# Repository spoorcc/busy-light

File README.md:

<div align="center">

# busy-light

**A Wi-Fi status ring for desks, doors and build rooms.**
Sixteen RGB LEDs that show your Jenkins build status or any other level, with no app and no cloud account.

-003399)

[Documentation](docs/README.md) ·
[Requirements](docs/requirements/needs.md) ·
[Architecture decisions](docs/decisions/) ·
[Roadmap](#roadmap) ·
[Contributing](CONTRIBUTING.md) ·
[Security](SECURITY.md)

</div>

---

> **Honest status:** busy-light is in the **design phase**. There is no released firmware, no manufactured
> hardware and no approved requirement set yet. Everything below describes the **intended** product and
> what the project has already proved with desk studies, PC prototypes and CAD experiments.
> Nothing here is certified, and no conformity with any regulation is claimed.

## What is it?

busy-light is a small round device with a ring of 16 individually controllable RGB LEDs. It joins your Wi-Fi,
listens to your build server or fetches its status over REST, and turns that into a colour or a level you can see
from across the room.

The first use case is a **Jenkins build light**: green, red, unstable, running, aborted. The second is a
**level gauge**: the ring fills like a dial from 0 to 100 percent for queue length, test pass rate, or any number
a REST endpoint can give.

## Why another status light?

Most status lights need a vendor app, a cloud account or a USB cable to a PC. busy-light is designed around a
different set of goals.

| Goal | What it means |
|------|---------------|
| **Works on a shared, untrusted network** | Per-unit access point password, encrypted provisioning, authenticated and signed updates. |
| **No app, no cloud** | Set-up and configuration through a web page served by the device itself. |
| **Small enough to put anywhere** | About 53 mm across, powered over USB-C. |
| **Cheap to build** | Target assembled board cost of EUR 10 to 20 with a prototype shop. |
| **Source-available and reproducible** | Software, hardware and mechanics are all in this repository, with generated files and checks that anyone can rerun. Code is Apache-2.0. Documentation, hardware and mechanics are free to copy and build for non-commercial use. |
| **Built like a product** | Requirements, decisions, risks and tests are traced from the first line, with EU market access (CE) in mind from day one. |

## Planned features

These are **planned**, taken from the draft requirements in [`docs/requirements/`](docs/requirements/). None is released.

- **16-LED RGB ring** with status colours, animations and a level (gauge) mode
- **Jenkins first:** receive pushed build events, or poll the Jenkins REST API
- **Mapping without code:** pick a value in the JSON answer, map it to a state or scale it to a level
- **Own access point for set-up:** the device creates a Wi-Fi network with a unique password printed on a label, you open a web page and enter your Wi-Fi details
- **Web interface** served by the device, no app to install
- **WPA2 and WPA2-Enterprise** networks, with user-loadable certificates
- **Over-the-air updates** that are signed and can be checked before they run
- **USB-C power** with safe handling of the available current: a hardware current limit and a firmware limiter on LED brightness
- **Secure boot and flash encryption** (planned for production units)

```mermaid
flowchart LR
    J[Jenkins or other REST source] -- push or poll --> D((busy-light))
    P[Phone or laptop] -- set-up page over the device's own Wi-Fi --> D
    D --> R[16-LED ring]
    U[USB-C] -- power --> D
```

## What exists today

The project has done a lot of thinking and some experiments, but **no product code or hardware yet**.

| Area | State |
|------|-------|
| Requirements | Written for needs, system, software, hardware and mechanics (101 entries). **18 are approved by the owner** (all 9 mechanical, 5 software, 3 hardware including the current-limit gate HW-010, 1 system); the rest are drafts. |
| Architecture decisions | 19 decision records. **17 are accepted** by the owner (ADR-0011, the housing, only for the prototype); 2 are superseded. Recent decisions: first antenna layout (ADR-0003), annular back bayonet (ADR-0014), AND gate for the fault readback (ADR-0018) and a standard-package regulator with a firmware current limit (ADR-0019). |
| Risk register | Open. Each risk has a mitigation and a verification link. |
| Reviews | Independent "goldfish" reviews recorded for the system design, the first spike plan and the hardware flow decision ([`docs/reviews/`](docs/reviews/)). |
| Software | Zephyr 4.5.0 workspace pinned. The input-current gate logic (`sw/app/src/gate.c`) has **20 host unit tests that pass** on `native_sim`; nothing runs on a board. A mapping extractor and an LED current limiter were tried as PC-only prototypes (results in the reports, code not in `sw/`). |
| Hardware | A scripted KiCad flow produces a **spike** full-board schematic (USB-C input, current-limit gate, hold-off, AND-gate fault readback, supply-pin surge protection, ESP32-C3 module, 16 LEDs) and a 4-layer board on the mechanical-spike outline, routed with Freerouting. The board is routed with **0 unconnected items** and passes the strict check apart from tolerated antenna and stand-in findings, but nothing is reviewed. Part datasheet evidence is recorded in a schema, **none verified**. The surge on the 5 V side is still to be **measured** on a built board. **No product schematic or layout yet.** |
| Mechanics | FreeCAD scripts generate the housing (base with USB-C window, button hole, PCB posts and snap hooks, annular back bayonet with lock lips and a mating accessory ring, lid with snap bumps), print coupons for the diffuser and the bayonet, and a tolerance check with tests. **Nothing printed or fit-tested**; the tolerances are assumptions. |
| Regulatory | Applicability analysis and compliance matrix started. No evidence collected, no declaration made. |

The reports behind these lines are in [`docs/verification/reports/`](docs/verification/reports/).

### Gallery

All images are generated from text sources or tool exports; none is hand-drawn. None shows a product design: they show the proposal and the experiments.

**Proposed software blocks** (PlantUML source in [`docs/diagrams/plantuml/`](docs/diagrams/plantuml/), draft architecture):

**Hardware spike (KiCad 10, generated by script, not reviewed, not the product design):**

| Schematic (spike), part 1: USB-C input, CC detection, current-step gate, hold-off, regulator |
|---|
|  |

| Schematic (spike), part 2: ESP32-C3 module, button, AND-gate fault readback, LED buffer, 16 LEDs |
|---|
|  |
| Two crops of one single-sheet schematic, exported with `kicad-cli`; click an image for full size. Some labels overlap (for example C1 and C27) and part values are open (`tbd`). The schematic is a spike under ADR-0012 (Proposed), not reviewed and not approved. |

| Board, 4 layers, top view (3D render) | Board, all copper layers and silkscreen |
|---|---|
|  |  |
| Generated by script from the schematic netlist on the outline of the mechanical spike. The 16 LED cells (one 2020 LED with its capacitor) are placed and routed as a symmetric ring by script; the rest is routed with Freerouting v2.5.0 (fine rules, 0.1 mm tracks, see ADR-0020, Proposed). | One run (ring14 run 9), picked as the best of 12 (routing is not deterministic); the board is stored in [`hw/kicad/spike-gate/board/`](hw/kicad/spike-gate/board/). **0 unconnected items, 0 hard findings.** The strict check lists 11 findings, all in the classes that the waiver list tolerates: 8 courtyard overlaps and 1 item inside the rule area (ESP32 antenna keep-out), 2 symbol mismatches (C3, C4). Power paths (analyst assumptions of 1.5, 1.0 and 0.5 A): 13.5, 18.0 and 22.7 mV drop. The fabricator-minimum check passes for the JLCPCB numbers of ADR-0020 (Proposed), with the via ring at the 0.15 mm minimum. Not run: antenna/RF, thermal, full fab review, bench. A spike result, **not** a reviewed board. |

Regenerate with [`hw/kicad/spike-gate/render_readme_images.sh`](hw/kicad/spike-gate/render_readme_images.sh). The 3D render has no component models for most parts and is not a fit check. See [`spike-pcb-placement-routing.md`](docs/verification/reports/spike-pcb-placement-routing.md).

| Housing model (FreeCAD script), exploded | Back of the base |
|---|---|
|  |  |
| Generated by [`mech/freecad/housing.py`](mech/freecad/housing.py) and [`accessory.py`](mech/freecad/accessory.py), drawn by [`mech/render_readme_images.sh`](mech/render_readme_images.sh). Parts: lid with snap bumps, base with USB-C window, button hole (working values, the switch is not chosen), posts, snap hooks and the bayonet groove with lock lips, stop and detent; the orange ring is the accessory with three T-lugs. The model passes its own checks (valid solids, no overlap, board fits, the lock holds and stops). **Nothing is printed or fit-tested**; the release tab is not modelled. Results: [`mech-housing-first-model.md`](docs/verification/reports/mech-housing-first-model.md). |

## Roadmap

| Phase | Goal | State |
|-------|------|-------|
| **0. Foundation** | Process, requirements, decisions, risks, regulatory outline, CI | in progress |
| **1. Spikes** | Prove the risky parts on a dev kit: Wi-Fi access point, web page, LED drive, power budget, secure boot | planned, waiting for approval of the spike plan |
| **2. Prototype** | 10 internal prototypes: schematic, board, housing, first firmware | planned |
| **3. Verify** | Test cases against approved requirements, pre-compliance tests | planned |
| **4. Release candidate** | Signed firmware, documentation, technical file | planned |

Dates are deliberately not given. Phases start when the previous one has evidence.

## How the project works

busy-light is run like a small regulated company, because the goal is a product that could be sold.

- **Specification before implementation.** No firmware, board or housing change without an approved requirement it traces to.
- **Decisions are recorded.** Costly choices get an architecture decision record with real alternatives, weighted criteria and a critical review.
- **Evidence over claims.** A result is only reported with its test or analysis. What was not run is stated.
- **Everything is code.** Diagrams, hardware (KiCad files generated from scripts) and mechanics (FreeCAD from scripts) are text sources with checks in CI.
- **Documentation is part of the product.** User documentation follows a controlled-language standard (ASD-STE100 principles).
- **EU market access from the start.** Cyber Resilience Act, Radio Equipment Directive, RoHS and friends are tracked in [`docs/regulatory/`](docs/regulatory/README.md). The project states which evidence exists and never states that the product "is compliant".

The full process is in [`docs/process/README.md`](docs/process/README.md).

## Repository layout

| Path | Contents |
|------|----------|
| [`sw/`](sw/) | Zephyr application, west manifest, tests |
| [`hw/`](hw/) | KiCad project, simulation, fabrication outputs, datasheets |
| [`mech/`](mech/) | FreeCAD models, exports, drawings, analysis |
| [`docs/`](docs/README.md) | Process, requirements, architecture, decisions, risk, verification, regulatory, user docs, standards |
| [`scripts/`](scripts/) | Traceability, documentation and CI check scripts |

## Getting started (developers)

**Software** (needs the Zephyr SDK and `west`):

```sh
west init -l sw
west update
west build -b <board> sw/app
```

**Repository checks:**

```sh
python3 -m venv --system-site-packages .venv
.venv/bin/pip install --group dev --group hw
python3 -I scripts/check_traceability.py     # requirements, decisions, risks and tests are linked
python3 -I scripts/check_docs_style.py       # user documentation style
scripts/build_diagrams.sh --check            # diagrams are up to date
.venv/bin/ruff check . && .venv/bin/pytest   # Python tooling
```

**Hardware and mechanical checks** run in CI through `scripts/ci_hw.sh` (KiCad 10) and `scripts/ci_mech.sh` (FreeCAD).
They report **NOT RUN** until product sources exist, so a skipped check is never mistaken for a pass.

## Contributing

Ideas, reviews and critical questions are welcome. Pull requests with code or documents are not accepted until the contributor terms have had a legal check. Please read [`CONTRIBUTING.md`](CONTRIBUTING.md) first.
A good first contribution is to challenge a draft requirement or a proposed decision in
[`docs/decisions/`](docs/decisions/): write down the alternative you would pick and why.

## Security

busy-light is designed for shared networks. To report a vulnerability, follow [`SECURITY.md`](SECURITY.md).
The planned vulnerability handling and key management are drafts under
[`docs/regulatory/technical-file/05-cybersecurity/`](docs/regulatory/technical-file/05-cybersecurity).

## License

| Part | Licence |
|------|---------|
| Code (firmware, scripts, generators, CI, assistant instructions in `.claude/`) | [Apache-2.0](LICENSES/Apache-2.0.txt) |
| Documentation, hardware, mechanics, images | [CC BY-NC-SA 4.0](LICENSES/CC-BY-NC-SA-4.0.txt) |
| Commercial use of the hardware, mechanics or documentation | Separate licence from the owner |

You may copy, study and build from the hardware and mechanical files for non-commercial purposes. Using a unit that you
bought is not restricted. The non-commercial parts are **source-available, not open source hardware**.
Details and the path-by-path map are in [`LICENSE.md`](LICENSE.md) and [`REUSE.toml`](REUSE.toml);
the decision is [ADR-0015](docs/decisions/ADR-0015-licensing-corrections.md). Third-party parts such as Zephyr keep their own licences.
This is not legal advice.

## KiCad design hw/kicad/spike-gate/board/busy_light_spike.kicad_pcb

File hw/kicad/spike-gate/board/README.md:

# Spike board result (HW-010)

The routed 4-layer spike board: ring14 run 9, picked from 12 runs (Freerouting 2.5.0 is not deterministic, so this is one run, not a recipe).
Made by `run_best.sh` with `SPIKE_PROFILE=fine`, `PLACE_GRID=1.0`, `PLACE_ANT_KEEPOUT=1`, `PLACE_BLOCKS=3`, `PLACE_ORIENT=1.5`, `SEED_OFFSET=200`, input netlist `full8` (not in the repo; regenerate with `run_full.sh`). Report: `docs/verification/reports/spike-pcb-placement-routing.md`.

Files: `busy_light_spike.kicad_pcb`, `.kicad_pro`, `.kicad_sch`, `.kicad_dru` (rules), `.placement.json`, `fp-lib-table` and `CUSTOM.pretty` (open the board next to them). Script output, never edited by hand.

Finishing (2026-11-08): the seven unannotated parts were renamed (`src/pcb_rename.py`: C1B to C1F are now C27 to C31, R_ILIM3B is R20, R_VD is R21), and silkscreen designators and four fiducials were added (`src/pcb_finish.py`; 27 parts have no free place for a designator). Routing did not change.

Checks run on this file (2026-11-08):
- strict gate `SPIKE_ALLOW_KNOWN_OPEN=0 python3 src/kicad_strict.py drc board/busy_light_spike.kicad_pcb stitched-4l`: 0 open items, only the tolerated classes: courtyards_overlap 8 (max 14, U9 antenna, DEV-004), items_not_allowed 1 (DEV-004);
- `src/pcb_fabcheck.py`: PASS against the JLCPCB numbers of ADR-0020, with the via ring at the absolute minimum (0.15 mm) on all 131 vias;
- `src/pcb_power_check.py`: 13.5 mV (VBUS_IC, 1.5 A), 18.0 mV (+5V, 1.0 A), 22.7 mV (+3V3, 0.5 A); the 50 mV target is an analyst assumption, not a requirement.

Capacitor values and spare (2026-11-08, owner decisions in `docs/verification/reports/proposal-tbd-capacitor-values.md`): C2 4.7u, C3 10u (0805), C5 2.2u, C6 10u; C4 and C32 are 1206 spares, not fitted (HW-016). `src/pcb_spare_caps.py` set the values, added C32 (bottom side, 24 mm from U7 pin 6 because the top side has no free place; C4 is 8.2 mm away, so the [5] mm of HW-016 is not met by either), marked both do-not-populate and wrote the sourcing fields to the footprints; `pcb_fix.py` routed C32 (one via, 13.7 mm of track, nothing else moved). The strict gate has no footprint mismatch any more; power drops unchanged (13.5, 18.0, 22.7 mV).

Not run: antenna/RF, thermal, a full fab review (Gerber, silkscreen, solder mask, assembly), bench. Open: ADR-0020 (fine rules) is Proposed; HW-014 to HW-016 are Draft. The test points are not in a row and the IC rotations are mixed. This is a spike result, not a reviewed or approved board; it is not "DFx approved" and not "fully functional".

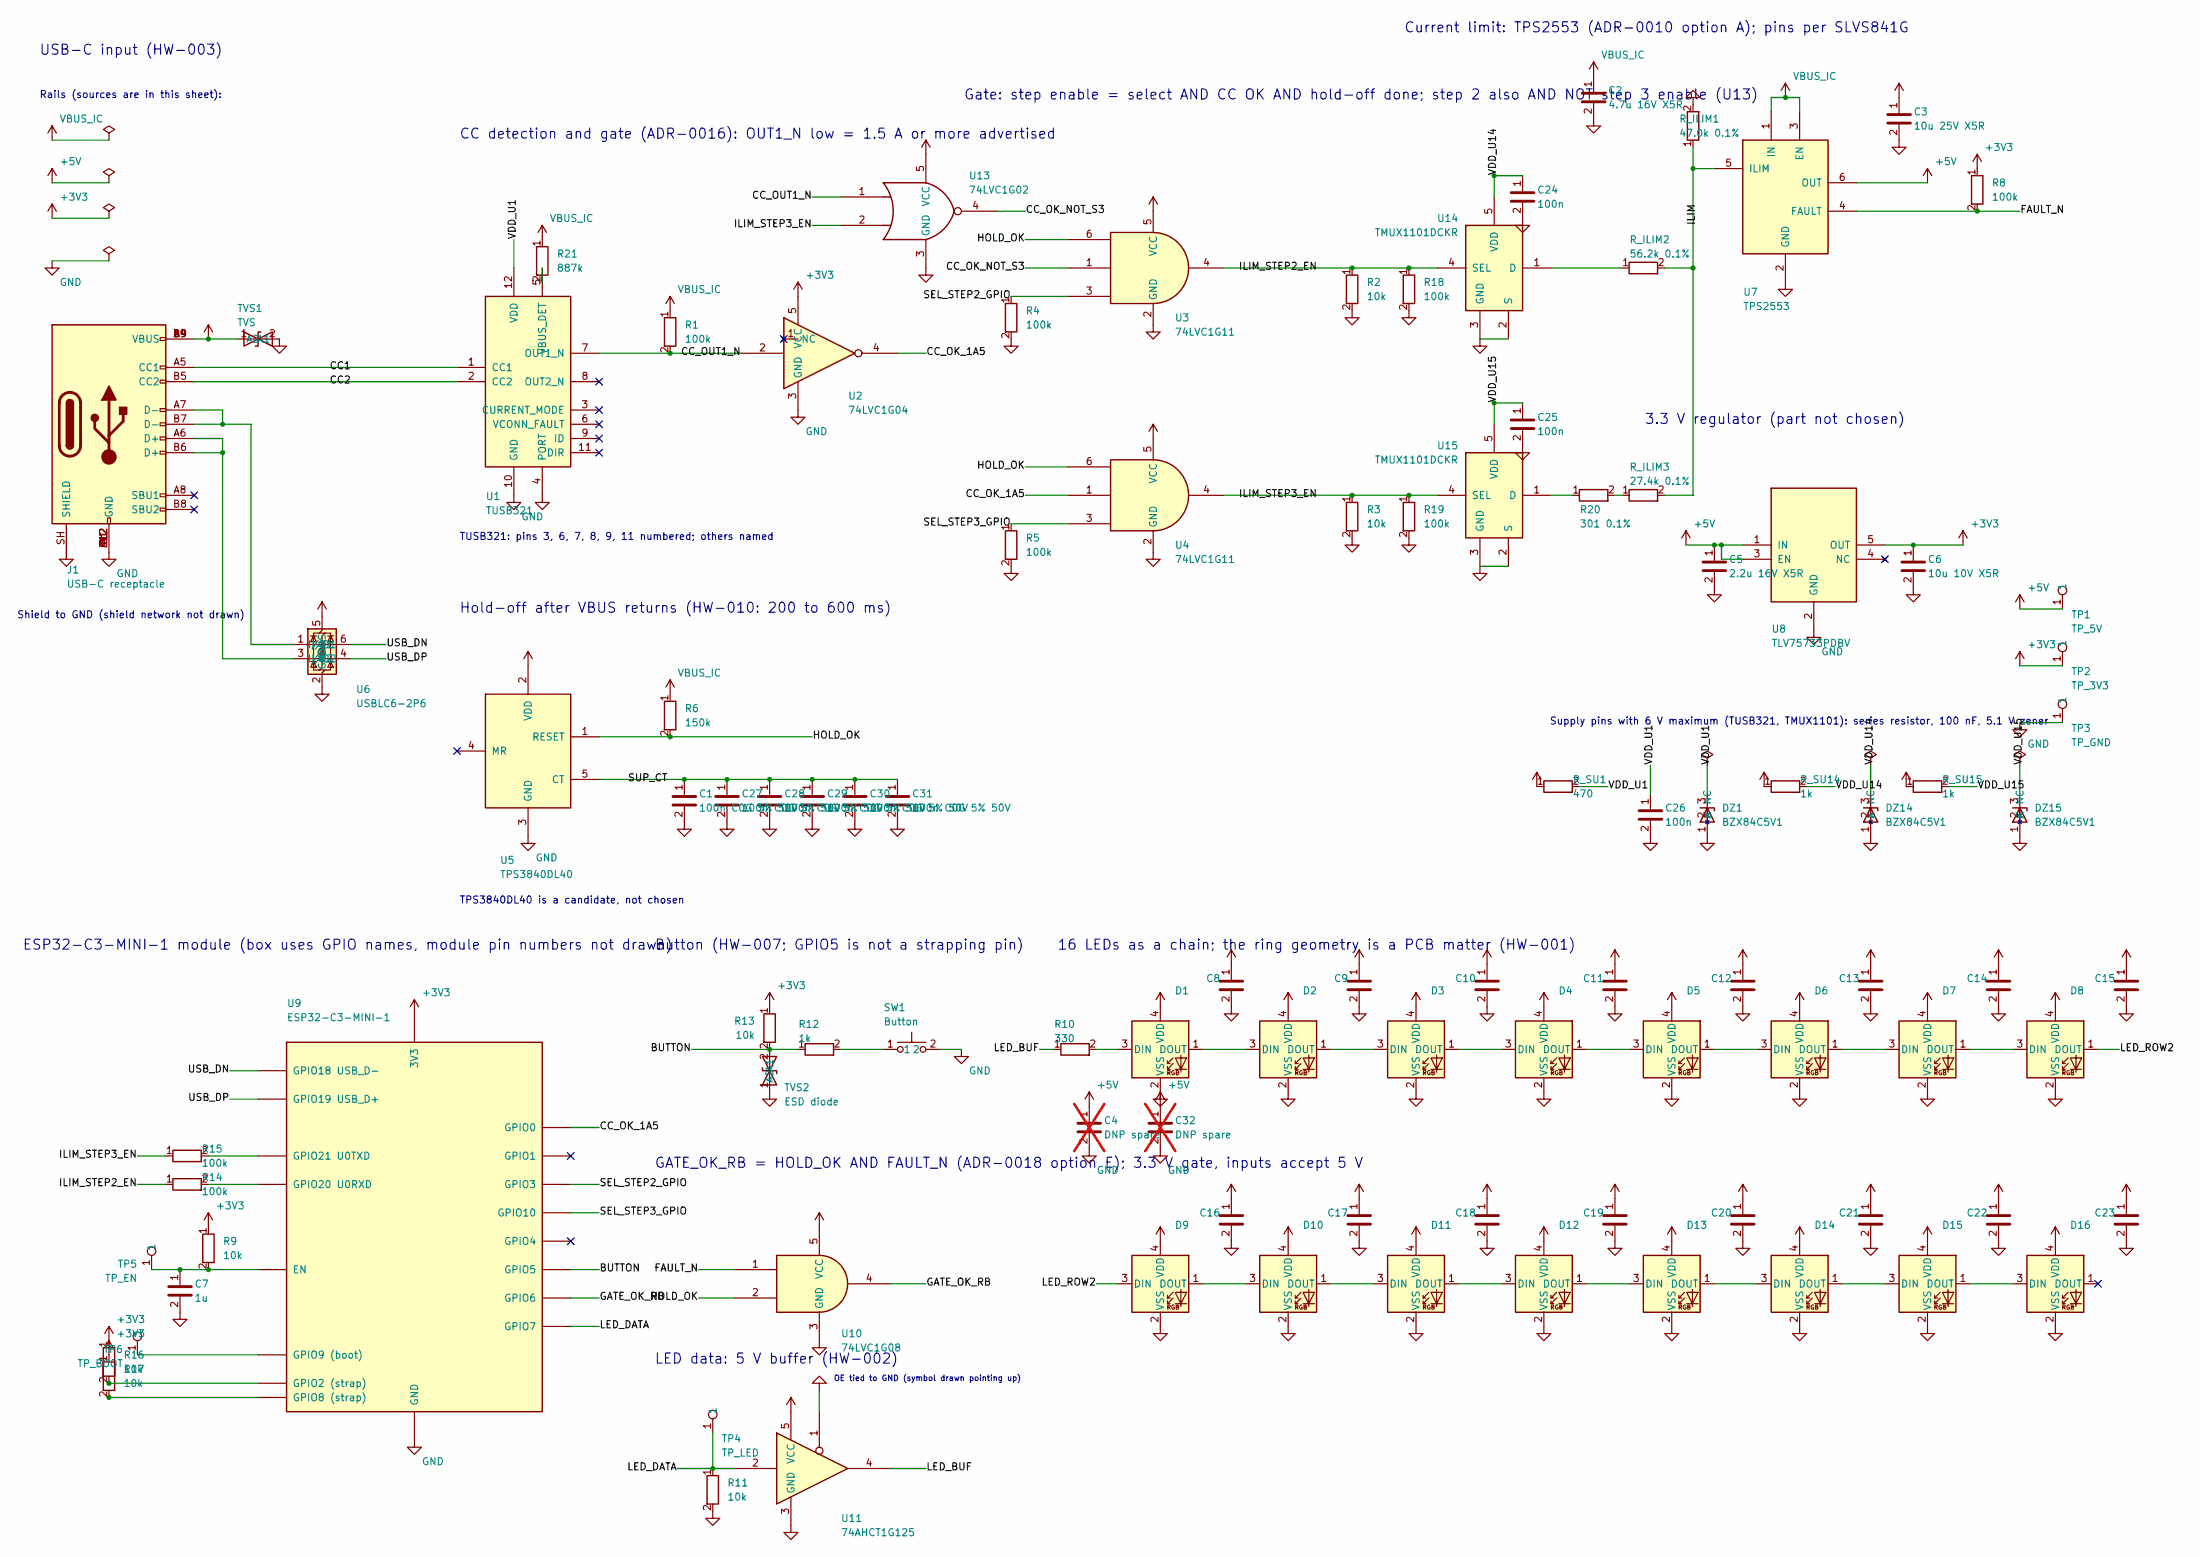
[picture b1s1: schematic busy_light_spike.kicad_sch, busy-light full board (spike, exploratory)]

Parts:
C1, C27, C28, C29, C30, C31: 100n C0G 5% 50V; C_1206_3216Metric; MPN GRM31C5C1H104JA01L; LCSC C97946
C2: 4.7u 16V X5R; C_0603_1608Metric; MPN CL10A475KO8NNNC; LCSC C19666
C3: 10u 25V X5R; C_0805_2012Metric; MPN CL21A106KAYNNNE; LCSC C15850
C4, C32: DNP spare; C_1206_3216Metric; not fitted
C5: 2.2u 16V X5R; C_0603_1608Metric; MPN CL10A225KO8NNNC; LCSC C23630
C6: 10u 10V X5R; C_0603_1608Metric; MPN CL10A106KP8NNNC; LCSC C19702
C7: 1u; C_0603_1608Metric; MPN CL10A105KB8NNNC; LCSC C15849
C8, C9, C10, C11, C12, C13, C14, C15, C16, C17, C18, C19, C20, C21, C22, C23, C24, C25, C26: 100n; C_0603_1608Metric; MPN CL10B104KB8NNNC; LCSC C1591
D1, D2, D3, D4, D5, D6, D7, D8, D9, D10, D11, D12, D13, D14, D15, D16: WS2812B; LED_WS2812B-2020_PLCC4_2.0x2.0mm; MPN WS2812B-2020; LCSC C965555
DZ1, DZ14, DZ15: BZX84C5V1; SOT-23; MPN BZX84-C5V1,215; LCSC C294621
J1: USB-C receptacle; USB_C_Receptacle_GCT_USB4085_edge
R1, R4, R5, R8, R14, R15, R18, R19: 100k; R_0603_1608Metric; MPN 0603WAF1003T5E; LCSC C25803
R2, R3, R9, R11, R13, R16, R17: 10k; R_0603_1608Metric; MPN 0603WAF1002T5E; LCSC C25804
R6: 150k; R_0603_1608Metric; MPN 0603WAF1503T5E; LCSC C22807
R10: 330; R_0603_1608Metric; MPN 0603WAF3300T5E; LCSC C23138
R12: 1k; R_0603_1608Metric; MPN 0603WAF1001T5E; LCSC C21190
R20: 301 0.1%; R_0603_1608Metric; MPN TD03G3010BT; LCSC C666860
R21: 887k; R_0603_1608Metric; MPN 0603WAF8873T5E; LCSC C23259
R_ILIM1: 47.0k 0.1%; R_0603_1608Metric; MPN TD03G4702BT; LCSC C667109
R_ILIM2: 56.2k 0.1%; R_0603_1608Metric; MPN TD03G5622BT; LCSC C667119
R_ILIM3: 27.4k 0.1%; R_0603_1608Metric; MPN RT0603BRE0727K4L
R_SU1: 470; R_0603_1608Metric; MPN 0603WAF4700T5E; LCSC C23179
R_SU14, R_SU15: 1k; R_0603_1608Metric; MPN 0603WAF1001T5E; LCSC C21190
SW1: Button; SW_SPST_TL3342; MPN TL3342F160QG; LCSC C2886898
TP1: TP_5V; TestPoint_Pad_D1.5mm
TP2: TP_3V3; TestPoint_Pad_D1.5mm
TP3: TP_GND; TestPoint_Pad_D1.5mm
TP4: TP_LED; TestPoint_Pad_D1.5mm
TP5: TP_EN; TestPoint_Pad_D1.5mm
TP6: TP_BOOT; TestPoint_Pad_D1.5mm
TVS1: TVS; D_SOD-323
TVS2: ESD diode; D_SOD-323
U1: TUSB321; X2QFN-12_RWB; MPN TUSB321RWBR; LCSC C139392
U2: 74LVC1G04; SOT-23-5; MPN SN74LVC1G04DBVR; LCSC C7827
U3, U4: 74LVC1G11; SOT-23-6; MPN SN74LVC1G11DBVR
U5: TPS3840DL40; SOT-23-5; MPN TPS3840DL40DBVR
U6: USBLC6-2P6; SOT-666; MPN USBLC6-2P6
U7: TPS2553; SOT-23-6; MPN TPS2553DBVR; LCSC C55266
U8: TLV75733PDBV; SOT-23-5; MPN TLV75733PDBVR; LCSC C485517
U9: ESP32-C3-MINI-1; MPN ESP32-C3-MINI-1-N4; LCSC C2838502
U10: 74LVC1G08; SOT-23-5; MPN SN74LVC1G08DBVR
U11: 74AHCT1G125; SOT-23-5; MPN SN74AHCT1G125DBVR
U13: 74LVC1G02; SOT-23-5; MPN SN74LVC1G02DBVR
U14, U15: TMUX1101DCKR; SOT-353_SC-70-5; MPN TMUX1101DCKR; LCSC C2673506

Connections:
+3V3: C6.1, R8.1, R9.1, R13.1, R16.1, R17.1, TP2.1, U2.5 (VCC), U3.5 (VCC), U4.5 (VCC), U8.5 (OUT), U9.3 (3V3), U10.5 (VCC), U13.5 (VCC)
+5V: C3.1, C4.1, C5.1, C8.1, C9.1, C10.1, C11.1, C12.1, C13.1, C14.1, C15.1, C16.1, C17.1, C18.1, C19.1, C20.1, C21.1, C22.1, C23.1, C32.1, D1.4 (VDD), D2.4 (VDD), D3.4 (VDD), D4.4 (VDD), D5.4 (VDD), D6.4 (VDD), D7.4 (VDD), D8.4 (VDD), D9.4 (VDD), D10.4 (VDD), D11.4 (VDD), D12.4 (VDD), D13.4 (VDD), D14.4 (VDD), D15.4 (VDD), D16.4 (VDD), TP1.1, U7.6 (OUT), U8.1 (IN), U8.3 (EN), U11.5 (VCC)
/BUTTON: R12.1, R13.2, TVS2.2 (A2), U9.19 (GPIO5)
/CC1: J1.A5 (CC1), U1.1 (CC1)
/CC2: J1.B5 (CC2), U1.2 (CC2)
/CC_OK_1A5: U2.4, U4.1, U9.12 (GPIO0)
/CC_OK_NOT_S3: U3.1, U13.4
/CC_OUT1_N: R1.2, U1.7 (OUT1_N), U2.2, U13.1
/FAULT_N: R8.2, U7.4 (FAULT), U10.1
/GATE_OK_RB: U9.20 (GPIO6), U10.4
/HOLD_OK: R6.2, U3.6, U4.6, U5.1 (RESET), U10.2
/ILIM: R_ILIM1.1, R_ILIM2.2, R_ILIM3.2, U7.5 (ILIM)
/ILIM_STEP2_EN: R2.1, R14.1, R18.1, U3.4, U14.4 (SEL)
/ILIM_STEP3_EN: R3.1, R15.1, R19.1, U4.4, U13.2, U15.4 (SEL)
/LED_BUF: R10.1, U11.4
/LED_DATA: R11.1, TP4.1, U9.21 (GPIO7), U11.2
/LED_ROW2: D8.1 (DOUT), D9.3 (DIN)
/SEL_STEP2_GPIO: R4.1, U3.3, U9.6 (GPIO3)
/SEL_STEP3_GPIO: R5.1, U4.3, U9.16 (GPIO10)
/SUP_CT: C1.1, C27.1, C28.1, C29.1, C30.1, C31.1, U5.5 (CT)
/USB_DN: U6.6 (I/O1), U9.26 (GPIO18 USB_D-)
/USB_DP: U6.4 (I/O2), U9.27 (GPIO19 USB_D+)
/VDD_U1: C26.1, DZ1.3 (K), R_SU1.2, U1.12 (VDD)
/VDD_U14: C24.1, DZ14.3 (K), R_SU14.2, U14.5 (VDD)
/VDD_U15: C25.1, DZ15.3 (K), R_SU15.2, U15.5 (VDD)
GND: C1.2, C2.2, C3.2, C4.2, C5.2, C6.2, C7.2, C8.2, C9.2, C10.2, C11.2, C12.2, C13.2, C14.2, C15.2, C16.2, C17.2, C18.2, C19.2, C20.2, C21.2, C22.2, C23.2, C24.2, C25.2, C26.2, C27.2, C28.2, C29.2, C30.2, C31.2, C32.2, D1.2 (VSS), D2.2 (VSS), D3.2 (VSS), D4.2 (VSS), D5.2 (VSS), D6.2 (VSS), D7.2 (VSS), D8.2 (VSS), D9.2 (VSS), D10.2 (VSS), D11.2 (VSS), D12.2 (VSS), D13.2 (VSS), D14.2 (VSS), D15.2 (VSS), D16.2 (VSS), DZ1.1 (A), DZ14.1 (A), DZ15.1 (A), J1.A1 (GND), J1.A12 (GND), J1.B1 (GND), J1.B12 (GND), J1.SH (SHIELD), R2.2, R3.2, R4.2, R5.2, R11.2, R18.2, R19.2, R_ILIM1.2, SW1.2, TP3.1, TVS1.2 (A2), TVS2.1 (A1), U1.4 (PORT), U1.10 (GND), U2.3 (GND), U3.2 (GND), U4.2 (GND), U5.3 (GND), U6.2 (GND), U7.2 (GND), U8.2 (GND), U9.1 (GND), U9.2 (GND), U9.11 (GND), U9.14 (GND), U9.36 (GND), U9.37 (GND), U9.38 (GND), U9.39 (GND), U9.40 (GND), U9.41 (GND), U9.42 (GND), U9.43 (GND), U9.44 (GND), U9.45 (GND), U9.46 (GND), U9.47 (GND), U9.48 (GND), U9.49 (GND), U9.50 (GND), U9.51 (GND), U9.52 (GND), U9.53 (GND), U10.3 (GND), U11.1, U11.3 (GND), U13.3 (GND), U14.2 (S), U14.3 (GND), U15.2 (S), U15.3 (GND)
unnamed: D1.3 (DIN), R10.2
unnamed: D1.1 (DOUT), D2.3 (DIN)
unnamed: D2.1 (DOUT), D3.3 (DIN)
unnamed: D3.1 (DOUT), D4.3 (DIN)
unnamed: D4.1 (DOUT), D5.3 (DIN)
unnamed: D5.1 (DOUT), D6.3 (DIN)
unnamed: D6.1 (DOUT), D7.3 (DIN)
unnamed: D7.1 (DOUT), D8.3 (DIN)
unnamed: D9.1 (DOUT), D10.3 (DIN)
unnamed: D10.1 (DOUT), D11.3 (DIN)
unnamed: D11.1 (DOUT), D12.3 (DIN)
unnamed: D12.1 (DOUT), D13.3 (DIN)
unnamed: D13.1 (DOUT), D14.3 (DIN)
unnamed: D14.1 (DOUT), D15.3 (DIN)
unnamed: D15.1 (DOUT), D16.3 (DIN)
unnamed: J1.A6 (D+), J1.B6 (D+), U6.3 (I/O2)
unnamed: J1.A7 (D-), J1.B7 (D-), U6.1 (I/O1)
unnamed: R12.2, SW1.1
unnamed: R20.2, R_ILIM3.1
unnamed: R21.2, U1.5 (VBUS_DET)
unnamed: C7.1, R9.2, TP5.1, U9.8 (EN)
unnamed: R16.2, U9.5 (GPIO2 (strap))
unnamed: R17.2, U9.22 (GPIO8 (strap))
unnamed: TP6.1, U9.23 (GPIO9 (boot))
unnamed: R14.2, U9.30 (GPIO20 U0RXD)
unnamed: R15.2, U9.31 (GPIO21 U0TXD)
unnamed: R_ILIM2.1, U14.1 (D)
unnamed: R20.1, U15.1 (D)
VBUS_IC: C2.1, J1.A4 (VBUS), J1.A9 (VBUS), J1.B4 (VBUS), J1.B9 (VBUS), R1.1, R6.1, R21.1, R_SU1.1, R_SU14.1, R_SU15.1, TVS1.1 (A1), U5.2 (VDD), U6.5 (VBUS), U7.1 (IN), U7.3 (EN)

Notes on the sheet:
USB-C input (HW-003)
CC detection and gate (ADR-0016): OUT1_N low = 1.5 A or more advertised
Gate: step enable = select AND CC OK AND hold-off done; step 2 also AND NOT step 3 enable (U13)
Hold-off after VBUS returns (HW-010: 200 to 600 ms)
Current limit: TPS2553 (ADR-0010 option A); pins per SLVS841G
3.3 V regulator (part not chosen)
TUSB321: pins 3, 6, 7, 8, 9, 11 numbered; others named
TPS3840DL40 is a candidate, not chosen
ESP32-C3-MINI-1 module (box uses GPIO names, module pin numbers not drawn)
Button (HW-007; GPIO5 is not a strapping pin)
GATE_OK_RB = HOLD_OK AND FAULT_N (ADR-0018 option E); 3.3 V gate, inputs accept 5 V
OE tied to GND (symbol drawn pointing up)
LED data: 5 V buffer (HW-002)
16 LEDs as a chain; the ring geometry is a PCB matter (HW-001)
Rails (sources are in this sheet):
Shield to GND (shield network not drawn)
Supply pins with 6 V maximum (TUSB321, TMUX1101): series resistor, 100 nF, 5.1 V zener

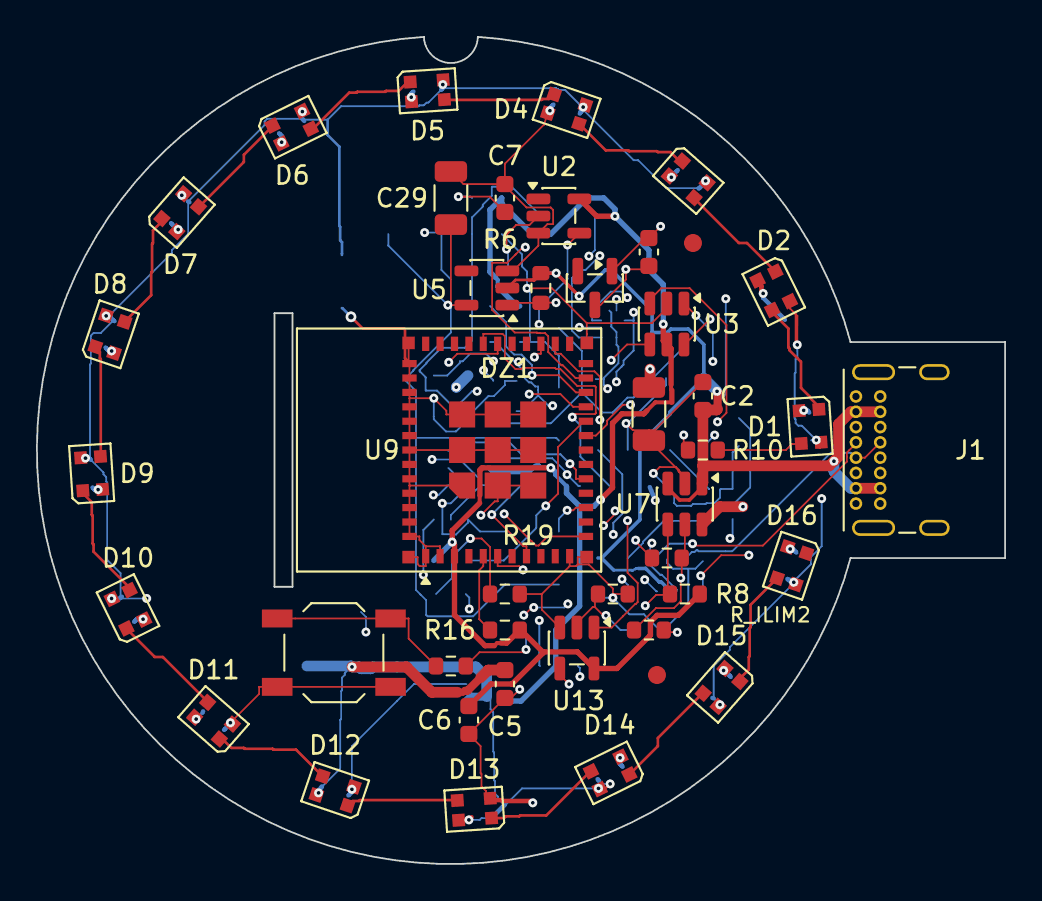
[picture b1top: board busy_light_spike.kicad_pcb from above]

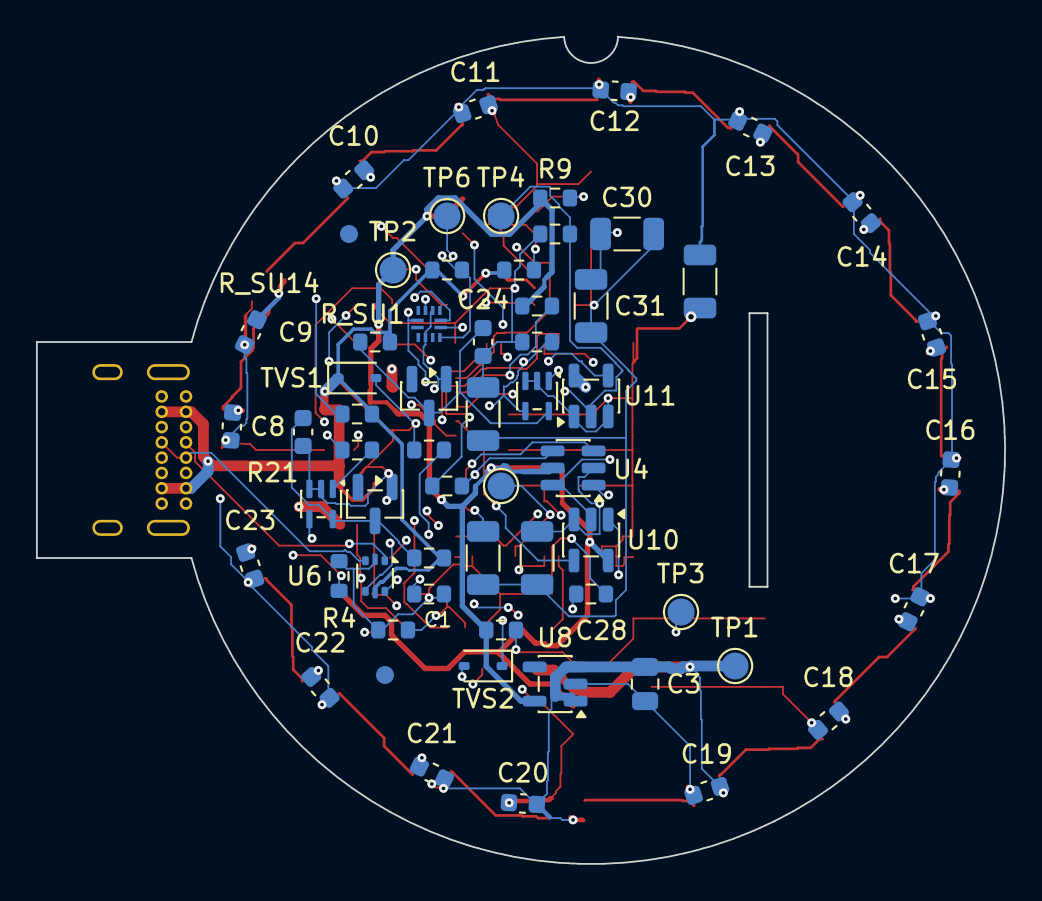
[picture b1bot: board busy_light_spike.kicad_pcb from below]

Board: 4 copper layers, 53.8 x 45.9 mm, 105 parts (62 on the bottom side), 55 nets.

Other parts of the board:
FID1, FID2, FID4, FID5: Fiducial

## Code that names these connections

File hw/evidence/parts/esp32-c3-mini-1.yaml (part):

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  name: IO2
  pin_type: io
  function: Strapping pin
  source: {page: 11, locator: Table 3-1, quote: 'IO2 5 I/O/T GPIO2, ADC1_CH2, FSPIQ'}
  aliases:
  - GPIO2
- id: ESP32-C3-MINI-1.pin.IO3
  pin: '6'
  name: IO3
  pin_type: io
  source: {page: 11, locator: Table 3-1, quote: 'IO3 6 I/O/T GPIO3, ADC1_CH3'}
  aliases:
  - GPIO3
- id: ESP32-C3-MINI-1.pin.EN
  pin: '8'
  name: EN
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  pin: '12'
  name: IO0
  pin_type: io
  source: {page: 11, locator: Table 3-1, quote: 'IO0 12 I/O/T GPIO0, ADC1_CH0, XTAL_32K_P'}
  aliases:
  - GPIO0
- id: ESP32-C3-MINI-1.pin.IO1
  pin: '13'
  name: IO1
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  pin: '16'
  name: IO10
  pin_type: io
  source: {page: 11, locator: Table 3-1, quote: 'IO10 16 I/O/T GPIO10, FSPICS0'}
  aliases:
  - GPIO10
- id: ESP32-C3-MINI-1.pin.IO4
  pin: '18'
  name: IO4
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  pin: '19'
  name: IO5
  pin_type: io
  source: {page: 11, locator: Table 3-1, quote: 'IO5 19 I/O/T GPIO5, ADC2_CH0, FSPIWP, MTDI'}
  aliases:
  - GPIO5
- id: ESP32-C3-MINI-1.pin.IO6
  pin: '20'
  name: IO6
  pin_type: io
  source: {page: 11, locator: Table 3-1, quote: 'IO6 20 I/O/T GPIO6, FSPICLK, MTCK'}
  aliases:
  - GPIO6
- id: ESP32-C3-MINI-1.pin.IO7
  pin: '21'
  name: IO7
  pin_type: io
  source: {page: 11, locator: Table 3-1, quote: 'IO7 21 I/O/T GPIO7, FSPID, MTDO'}
  aliases:
  - GPIO7
- id: ESP32-C3-MINI-1.pin.IO8
  pin: '22'
  name: IO8
  pin_type: io
  function: Strapping pin
  source: {page: 11, locator: Table 3-1, quote: IO8 22 I/O/T GPIO8}
  aliases:
  - GPIO8
- id: ESP32-C3-MINI-1.pin.IO9
  pin: '23'
  name: IO9
  pin_type: io
  function: Strapping pin, boot button
  source: {page: 11, locator: Table 3-1, quote: IO9 23 I/O/T GPIO9}
  aliases:
  - GPIO9
- id: ESP32-C3-MINI-1.pin.IO18
  pin: '26'
  name: IO18
  pin_type: io
  function: USB D-
  source: {page: 11, locator: Table 3-1, quote: 'IO18 26 I/O/T GPIO18, USB_D-'}
  aliases:
  - GPIO18
  - GPIO18 USB_D-
- id: ESP32-C3-MINI-1.pin.IO19
  pin: '27'
  name: IO19
  pin_type: io
  function: USB D+
  source: {page: 11, locator: Table 3-1, quote: 'IO19 27 I/O/T GPIO19, USB_D+'}
  aliases:
  - GPIO19
  - GPIO19 USB_D+
- id: ESP32-C3-MINI-1.pin.RXD0
  pin: '30'
  name: RXD0
  pin_type: io
  function: UART0 RX
  source: {page: 11, locator: Table 3-1, quote: 'RXD0 30 I/O/T GPIO20, U0RXD'}
  aliases:
  - GPIO20
  - GPIO20 U0RXD
- id: ESP32-C3-MINI-1.pin.TXD0
  pin: '31'
  name: TXD0
  pin_type: io
  function: UART0 TX
  source: {page: 11, locator: Table 3-1, quote: 'TXD0 31 I/O/T GPIO21, U0TXD'}
  aliases:
  - GPIO21
  - GPIO21 U0TXD
claims:
- id: ESP32-C3-MINI-1.abs_max_vdd33
  parameter: Power supply voltage VDD33
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  statement: The EN pin must not float.
  source: {page: 11, locator: Table 3-1, quote: 'Note: Do not leave the EN pin floating.'}
- id: ESP32-C3-MINI-1.strap_gpio9
  parameter: Default strapping state of GPIO9
  category: function
  statement: GPIO9 has a weak pull-up at reset (bit value 1); GPIO2 and GPIO8 float by default.
  source: {page: 12, locator: Table 4-1, quote: GPIO9 Weak pull-up 1}
- id: ESP32-C3-MINI-1.drive_usb_pins
  parameter: Default drive strength of GPIO18 and GPIO19
  category: electrical
  typ: 40
  unit: mA
  notes: From the ESP32-C3 chip datasheet, not the module datasheet. Footnote lists the default drive strength per pin; other pins 20 mA, GPIO2/GPIO3/MTMS/MTDI 10 mA.
  source: {page: 17, locator: Table 2-1 note 4, quote: 'GPIO18, GPIO19: 40 mA', document: esp32-c3-ds}
- id: ESP32-C3-MINI-1.abs_max_input_power_pins
  parameter: Input power pins, allowed input voltage (chip)
  category: abs_max
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

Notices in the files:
hw/evidence/parts/esp32-c3-mini-1.yaml:
SPDX-License-Identifier: CC-BY-NC-SA-4.0
README.md:
Docs, hardware, mechanics: CC BY-NC-SA 4.0
